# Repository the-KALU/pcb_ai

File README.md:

# PCB-AI

An AI pipeline for generating and optimizing PCB layouts from natural language prompts.

## Project Structure

- `scripts/`: Parsing, training, and testing scripts
- `pcb_projects/`: KiCad files
- `models/`: Saved models

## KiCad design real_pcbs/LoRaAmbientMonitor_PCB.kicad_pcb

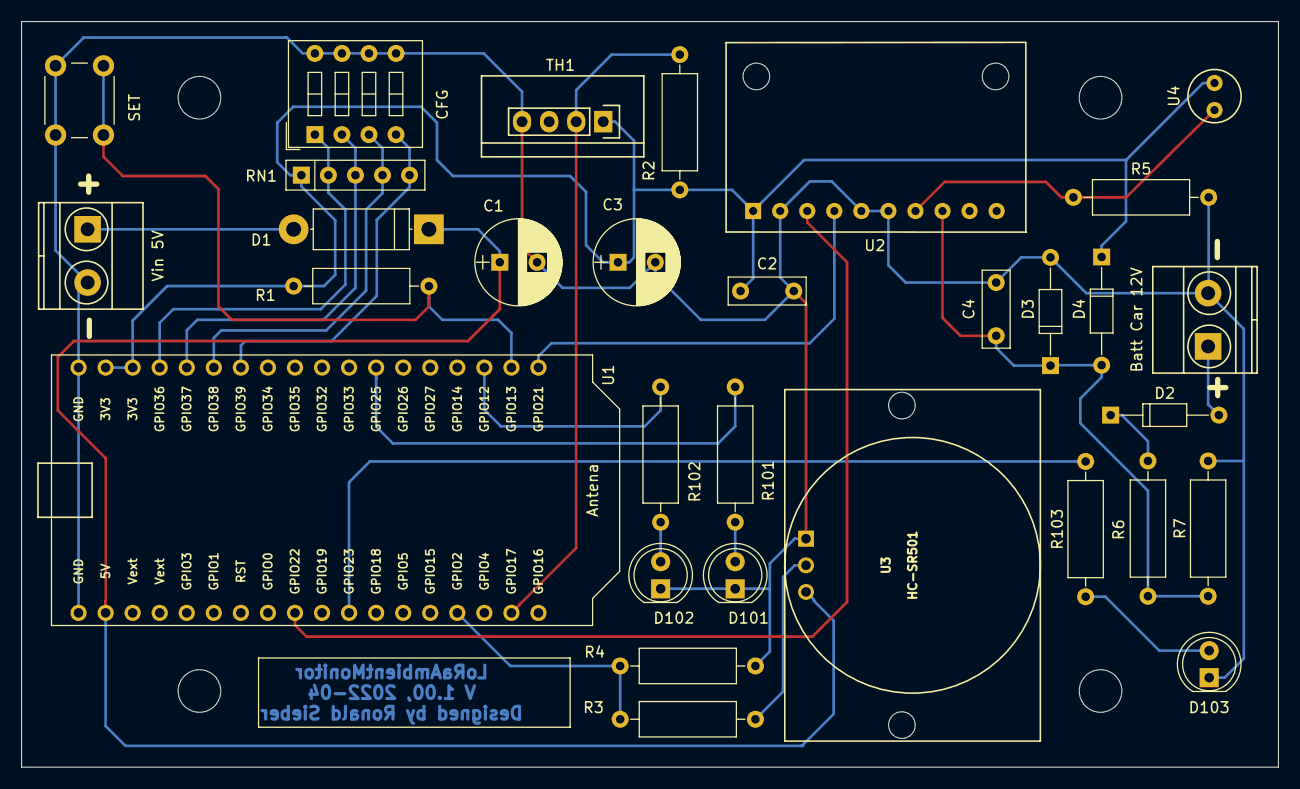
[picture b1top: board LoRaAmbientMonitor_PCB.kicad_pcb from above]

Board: 2 copper layers, 118.0 x 70.0 mm, 31 parts (0 on the bottom side), 24 nets.

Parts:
C1: 100µF; CP_Radial_D8.0mm_P3.50mm
C2, C4: 1µF; C_Rect_L7.2mm_W2.5mm_P5.00mm_FKS2_FKP2_MKS2_MKP2
C3: 47µF; CP_Radial_D8.0mm_P3.50mm
D1: 1N4001; D_5W_P12.70mm_Horizontal
D2: 1N4148; D_DO-35_SOD27_P10.16mm_Horizontal
D3: ZF4,7; D_DO-35_SOD27_P10.16mm_Horizontal
D4: BAT42; D_DO-35_SOD27_P10.16mm_Horizontal
D101, D102, D103: LED; LED_D5.0mm
J1: Vin 5V; TerminalBlock_Phoenix_MKDS1.5-2pol
J2: Batt Car 12V; TerminalBlock_Phoenix_MKDS1.5-2pol
R1, R2, R4: 4k7; R_Axial_DIN0309_L9.0mm_D3.2mm_P12.70mm_Horizontal
R3: 2k7; R_Axial_DIN0309_L9.0mm_D3.2mm_P12.70mm_Horizontal
R5: 100k; R_Axial_DIN0309_L9.0mm_D3.2mm_P12.70mm_Horizontal
R6: 68k; R_Axial_DIN0309_L9.0mm_D3.2mm_P12.70mm_Horizontal
R7: 18k; R_Axial_DIN0309_L9.0mm_D3.2mm_P12.70mm_Horizontal
R101, R102, R103: 470R; R_Axial_DIN0309_L9.0mm_D3.2mm_P12.70mm_Horizontal
RN1: SIL 5-4 4,7K; R_Array_SIP5
SW1: SET; SW_PUSH_6mm_h5mm
SW2: CFG; SW_DIP_x4_W7.62mm_Slide
TH1: DHT22; DHT22_Temperature_Humidity
U1: Heltec_WiFi_LoRa_V2_L; Heltec_WiFi_LoRa_V2
U2: Adafruit_ADS1115
U3: HC-SR501
U4: ALS-PDIC243

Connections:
+3V3: C2.1, C3.1, D4.1, R1.1, R2.2, RN1.1, TH1.1, U1.34, U1.35, U2.1, U4.1
+5V: C1.1, D1.1, U1.2, U3.3
GND: C1.2, C2.2, C3.2, C4.2, D3.2, D101.1, D102.1, D103.1, J1.2, J2.2, R4.2, R5.2, R7.2, SW1.2, SW2.5, SW2.6, SW2.7, SW2.8, TH1.4, U1.1, U1.36, U2.2, U2.5, U2.6, U3.1
unnamed: C4.1, D3.1, D4.2, R6.2, R7.1, U2.8
unnamed: D1.2, J1.1
unnamed: D2.1, R6.1
unnamed: D2.2, J2.1
unnamed: D101.2, R101.1
unnamed: D102.2, R102.1
unnamed: D103.2, R103.1
unnamed: R1.2, SW1.1, U1.20
unnamed: R2.1, TH1.2, U1.17
unnamed: R3.1, U3.2
unnamed: R3.2, R4.1, U1.15
unnamed: R5.1, U2.7, U4.2
unnamed: R101.2, U1.25
unnamed: R102.2, U1.21
unnamed: R103.2, U1.11
unnamed: RN1.2, SW2.1, U1.33
unnamed: RN1.3, SW2.2, U1.32
unnamed: RN1.4, SW2.3, U1.31
unnamed: RN1.5, SW2.4, U1.30
unnamed: U1.9, U2.3
unnamed: U1.19, U2.4

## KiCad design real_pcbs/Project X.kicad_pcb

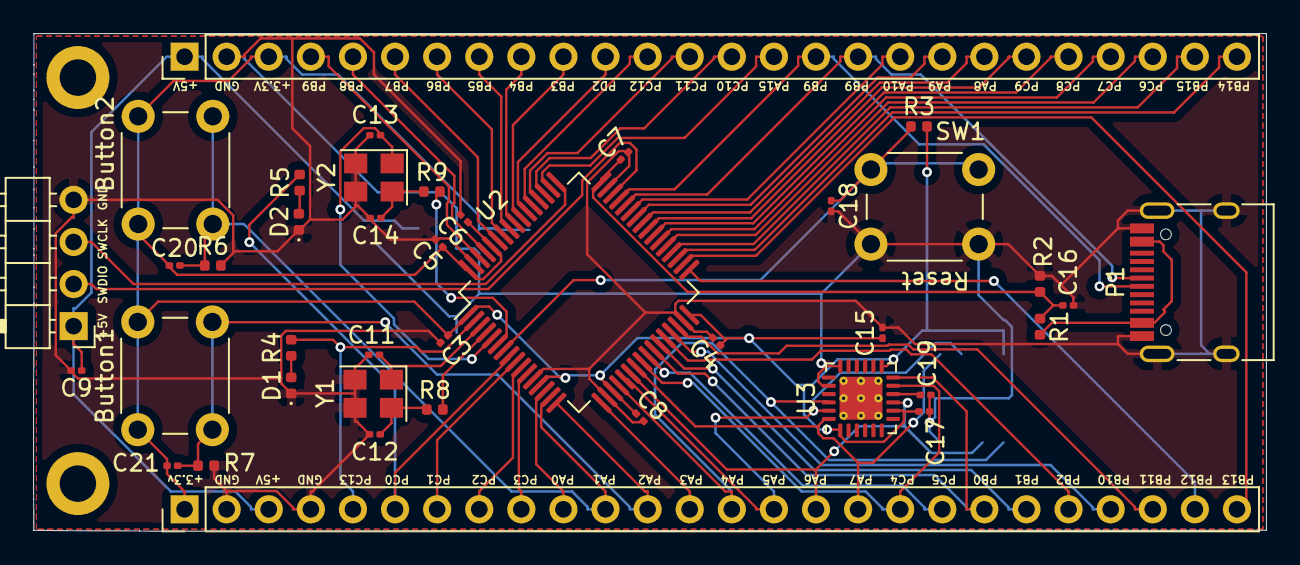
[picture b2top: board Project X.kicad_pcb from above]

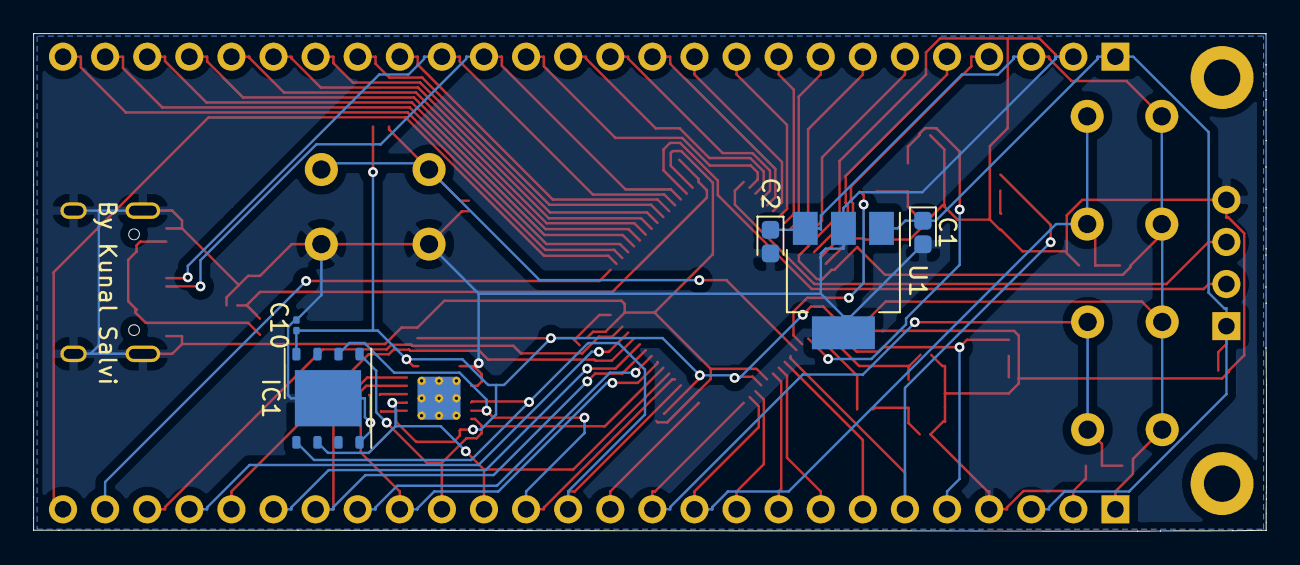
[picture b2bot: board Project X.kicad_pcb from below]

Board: 2 copper layers, 74.4 x 30.0 mm, 46 parts (5 on the bottom side), 62 nets.

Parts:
Button1, Button2: SW_SPST; SW_PUSH_6mm_H5mm
C1, C2: 3.3U; CP_EIA-1608-08_AVX-J
C3, C4, C5, C6, C7, C8, C9: 100N; C_0201_0603Metric
C10, C15, C16, C18, C20, C21: 10N; C_0201_0603Metric
C11, C12, C13, C14: 50P; C_0201_0603Metric
C17, C19: 0.1U; C_0201_0603Metric
D1, D2: LED; LED_0402_1005Metric
IC1: W25Q128JVPIQ; WSON-8-1EP_6x5mm_P1.27mm_EP3.4x4mm
J1: Conn_01x04; PinHeader_1x04_P2.54mm_Horizontal
J2, J3: Conn_01x26; PinHeader_1x26_P2.54mm_Vertical
P1: USB_C_Plug_USB2.0; USB_C_Receptacle_HRO_TYPE-C-31-M-12
R1: 1.1K; R_0402_1005Metric
R2: 2K; R_0402_1005Metric
R3, R4, R5, R6, R7: 4.7K; R_0402_1005Metric
R8, R9: 1M; R_0402_1005Metric
SW1: SW_SPST; SW_PUSH_6mm_H5mm
U1: LT1129-3.3_SOT223; SOT-223-3_TabPin2
U2: STM32L476RCTx; LQFP-64_10x10mm_P0.5mm
U3: MPU-9250; QFN-24-1EP_4x4mm_P0.5mm_EP2.6x2.6mm_ThermalVias
Y1: 8MHz; Crystal_SMD_3225-4Pin_3.2x2.5mm
Y2: 32.768K; Crystal_SMD_3225-4Pin_3.2x2.5mm
mouse-bite-2mm-slot: VAL**; mouse-bite-2mm-slot

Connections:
+3V3: Button1.1, Button2.1, C2.1, C3.1, C4.1, C5.1, C6.1, C8.1, C10.1, C15.1, C17.1, C20.1, C21.1, IC1.8, J2.1, J3.3, R3.1, U1.3, U2.1, U2.13, U2.19, U2.32, U2.60, U2.64, U3.1, U3.8, U3.13
+5V: C1.1, C9.1, J1.1, J2.3, J3.1, U1.1
/D+: J3.16, P1.A6, U2.45
/D-: J3.17, P1.A7, U2.44
/NRST: C18.1, R3.2, SW1.1, U2.7
/OSC8_IN: C13.1, U2.5, Y2.1
/OSC8_OUT: R9.2, U2.6
/OSC32_IN: C11.1, U2.3, Y1.1
/OSC32_OUT: R8.2, U2.4
/PA0: J2.10, U2.14
/PA1: Button2.2, C20.2, J2.11, R6.1, U2.15
/PA2: Button1.2, C21.2, J2.12, R7.1, U2.16
/PA3: J2.13, U2.17
/PA4: IC1.1, J2.14, U2.20, U3.22
/PA5: IC1.6, J2.15, U2.21, U3.23
/PA6: IC1.2, J2.16, U2.22, U3.9
/PA7: IC1.5, J2.17, U2.23, U3.24
/PA8: J3.20, U2.41
/PA9: J3.19, U2.42
/PA10: J3.18, U2.43
/PA15: J3.15, U2.50
/PB0: J2.20, U2.26, U3.12
/PB1: J2.21, U2.27
/PB2: J2.22, U2.28
/PB3: J3.10, U2.55
/PB4: J3.9, U2.56
/PB5: J3.8, U2.57
/PB6: J3.7, U2.58
/PB7: J3.6, U2.59
/PB8: J3.5, U2.61
/PB9: J3.4, U2.62
/PB10: J2.23, U2.29
/PB11: J2.24, U2.30
/PB12: J2.25, U2.33
/PB13: J2.26, U2.34
/PB14: J3.26, U2.35
/PB15: J3.25, U2.36
/PC0: J2.6, R5.2, U2.8
/PC1: J2.7, U2.9
/PC2: J2.8, U2.10
/PC3: J2.9, U2.11
/PC4: J2.18, U2.24, U3.11
/PC5: J2.19, U2.25
/PC6: J3.24, U2.37
/PC7: J3.23, U2.38
/PC8: J3.22, U2.39
/PC9: J3.21, U2.40
/PC10: J3.14, U2.51
/PC11: J3.13, U2.52
/PC12: J3.12, U2.53
/PC13: J2.5, R4.2, U2.2
/PD2: J3.11, U2.54
/SWCLK: J1.3, U2.49
/SWDIO: J1.2, U2.46
/VBUS: C7.1, C16.1, R1.1, R2.2, U2.48
GND: C1.2, C2.2, C3.2, C4.2, C5.2, C6.2, C7.2, C8.2, C9.2, C10.2, C11.2, C12.2, C13.2, C14.2, C15.2, C16.2, C17.2, C18.2, C19.1, D1.1, D2.1, IC1.4, IC1.9, J1.4, J2.2, J2.4, J3.2, P1.A1, P1.A12, P1.B1, P1.B12, P1.S1, R2.1, R6.2, R7.2, SW1.2, U1.2, U2.12, U2.18, U2.31, U2.47, U2.63, U3.18, U3.20, Y1.2, Y1.3, Y2.2, Y2.3
unnamed: C12.1, R8.1, Y1.4
unnamed: C14.1, R9.1, Y2.4
unnamed: C19.2, U3.10
unnamed: D1.2, R4.1
unnamed: D2.2, R5.1
unnamed: P1.A4, P1.A9, P1.B4, P1.B9, R1.2

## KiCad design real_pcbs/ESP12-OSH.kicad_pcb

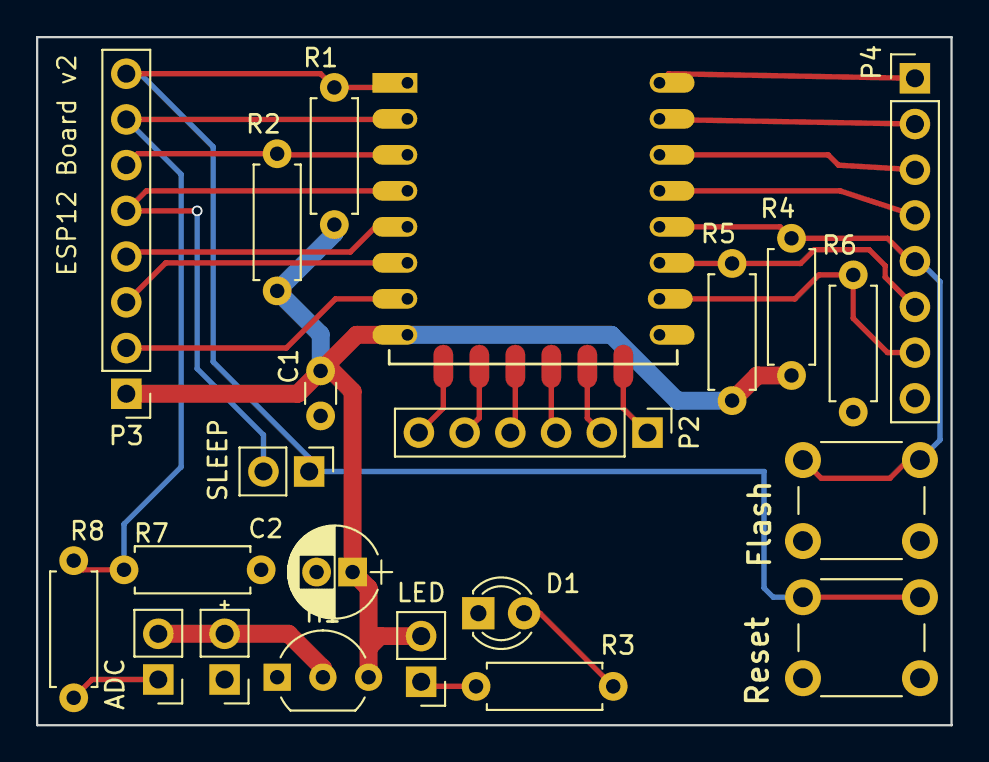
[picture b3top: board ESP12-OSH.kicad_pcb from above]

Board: 2 copper layers, 50.8 x 38.2 mm, 23 parts (1 on the bottom side), 26 nets.

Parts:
ADC: Jumper; Pin_Header_Straight_1x02_Pitch2.54mm
C1: 100nF; C_Disc_D3.0mm_W1.6mm_P2.50mm
C2: 0.1uF; CP_Radial_D5.0mm_P2.00mm
D1: LED; LED_D3.0mm
H1: HT7333; TO-92_Inline_Wide
IN: CONN_01X02; Pin_Header_Straight_1x02_Pitch2.54mm
LED: Jumper; Pin_Header_Straight_1x02_Pitch2.54mm
LOGO: newlogo
P2: CONN_01X06; Pin_Header_Straight_1x06_Pitch2.54mm
P3, P4: CONN_01X08; Pin_Header_Straight_1x08_Pitch2.54mm
R1, R2, R4, R5, R6: 10K; R_Axial_DIN0207_L6.3mm_D2.5mm_P7.62mm_Horizontal
R3: 1K; R_Axial_DIN0207_L6.3mm_D2.5mm_P7.62mm_Horizontal
R7: 100K; R_Axial_DIN0207_L6.3mm_D2.5mm_P7.62mm_Horizontal
R8: 470K; R_Axial_DIN0207_L6.3mm_D2.5mm_P7.62mm_Horizontal
SLEEP: Jumper; Pin_Header_Straight_1x02_Pitch2.54mm
SW1, SW2: SW_Push; SW_PUSH_6mm
U1: ESP-12E

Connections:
/ADC: P3.7, R7.1, R8.2, U1.2
/CH_PD: P3.6, R2.1, U1.3
/CSO: P2.6, U1.17
/GPIO0: P4.5, R4.2, SW2.1, U1.12
/GPIO2: P4.6, R5.2, U1.11
/GPIO4: P4.4, U1.13
/GPIO5: P4.3, U1.14
/GPIO09: P2.4, U1.19
/GPIO10: P2.3, U1.20
/GPIO12: P3.3, U1.6
/GPIO13: P3.2, U1.7
/GPIO14: P3.4, U1.5
/GPIO15: P4.7, R6.2, U1.10
/GPIO16: P3.5, SLEEP.2, U1.4
/MISO: P2.5, U1.18
/MOSI: P2.2, U1.21
/REST: P3.8, R1.1, SLEEP.1, SW1.1, U1.1
/RX: P4.2, U1.15
/SCLK: P2.1, U1.22
/TX: P4.1, U1.16
/VCC: C1.1, C2.1, H1.3, LED.2, P3.1, R1.2, R2.2, R4.1, R5.1, U1.8
/VIN: ADC.2, H1.2, IN.2
GND: C1.2, C2.2, D1.1, H1.1, IN.1, P4.8, R6.1, R7.2, SW1.2, SW2.2, U1.9
unnamed: D1.2, R3.2
unnamed: LED.1, R3.1
unnamed: ADC.1, R8.1

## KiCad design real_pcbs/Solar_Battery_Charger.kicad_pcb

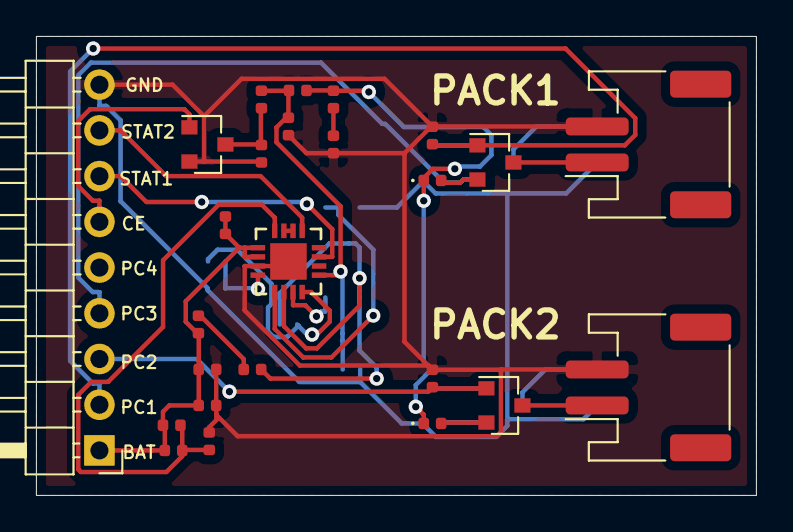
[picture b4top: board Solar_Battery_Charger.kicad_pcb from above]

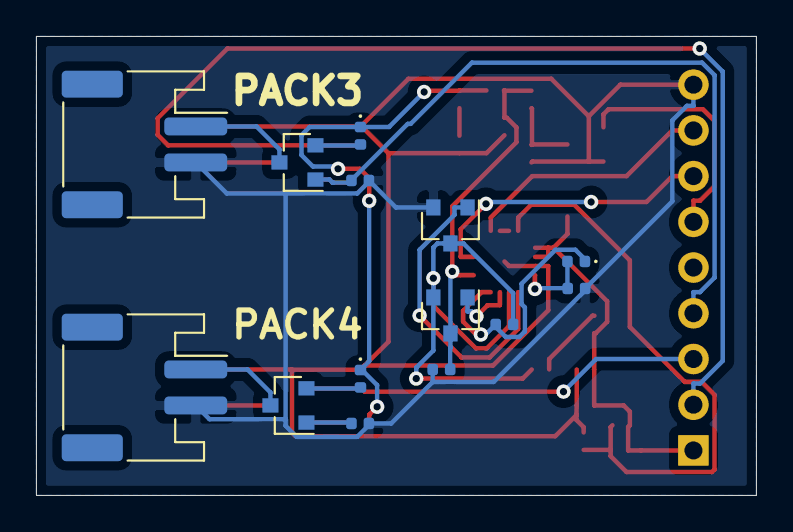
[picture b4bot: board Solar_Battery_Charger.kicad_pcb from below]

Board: 2 copper layers, 40.0 x 25.5 mm, 39 parts (14 on the bottom side), 29 nets.

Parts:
C1: 2.2U; C_0402_1005Metric
C2, C4: 1U; C_0402_1005Metric
C5, C7: 0.1U; C_0402_1005Metric
C6, C8: 10U; C_0402_1005Metric
C9: 4.7U; C_0402_1005Metric
C10: 22P; C_0402_1005Metric
D1, D2, D3, D4: D; D_0402_1005Metric
D5: D_Schottky; D_0402_1005Metric
J1, J2, J3, J4: Conn_01x02; JST_PH_S2B-PH-SM4-TB_1x02-1MP_P2.00mm_Horizontal
J5: Conn_01x09; PinHeader_1x09_P2.54mm_Horizontal
L1: 10U; L_0402_1005Metric
Q1, Q2, Q3, Q4, Q5, Q6, Q7: 2N7002; SOT-23
R1: 100K; R_0402_1005Metric
R2, R3: 499K; R_0402_1005Metric
R4: 36K; R_0402_1005Metric
R5: 2; R_0402_1005Metric
R6: 10; R_0402_1005Metric
RMOS1, RMOS2, RMOS3, RMOS4: 10K; R_0402_1005Metric
RSR1: 20m; R_0402_1005Metric
U1: BQ24650RVAR; QFN50P350X350X100-17N

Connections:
BATTERY_PACK: C7.1, C7.2, C8.1, C9.1, C10.1, J5.1, R2.1, RSR1.2, U1.9, U1.10
BTST: C5.2, D5.1, U1.16
CE: J5.6, Q3.1
GND: C1.2, C2.2, C4.1, C6.2, C8.2, C9.2, J1.2, J2.2, J3.2, J4.2, J5.9, Q2.2, Q3.2, R1.2, R4.1, RMOS1.2, RMOS2.2, RMOS3.2, RMOS4.2, U1.11, U1.17
unnamed: C1.1, R5.1
unnamed: D1.1, D2.1, D3.1, D4.1, R5.2, R6.2
unnamed: D1.2, Q4.2
unnamed: D2.2, Q5.2
unnamed: D3.2, Q6.2
unnamed: D4.2, Q7.2
unnamed: J1.1, Q4.3
unnamed: J2.1, Q5.3
unnamed: J3.1, Q6.3
unnamed: J4.1, Q7.3
unnamed: L1.2, RSR1.1
unnamed: Q1.1, U1.15
unnamed: Q2.1, U1.13
unnamed: Q3.3, R3.1, R4.2, U1.2
unnamed: U1.6, U1.7
PACK1_CONTROL: J5.2, Q4.1, RMOS1.1
PACK2_CONTROL: J5.3, Q5.1, RMOS2.1
PACK3_CONTROL: J5.4, Q6.1, RMOS3.1
PACK4_CONTORL: Q7.1, RMOS4.1
PH: C5.1, L1.1, Q1.2, Q2.3, U1.14
REGN: C4.2, D5.2, U1.12
STAT1: J5.7, U1.3
STAT2: J5.8, U1.5
VCC_PACK: C2.1, C6.1, Q1.3, R3.2, R6.1, U1.1
VFB: C10.2, R1.1, R2.2, U1.8

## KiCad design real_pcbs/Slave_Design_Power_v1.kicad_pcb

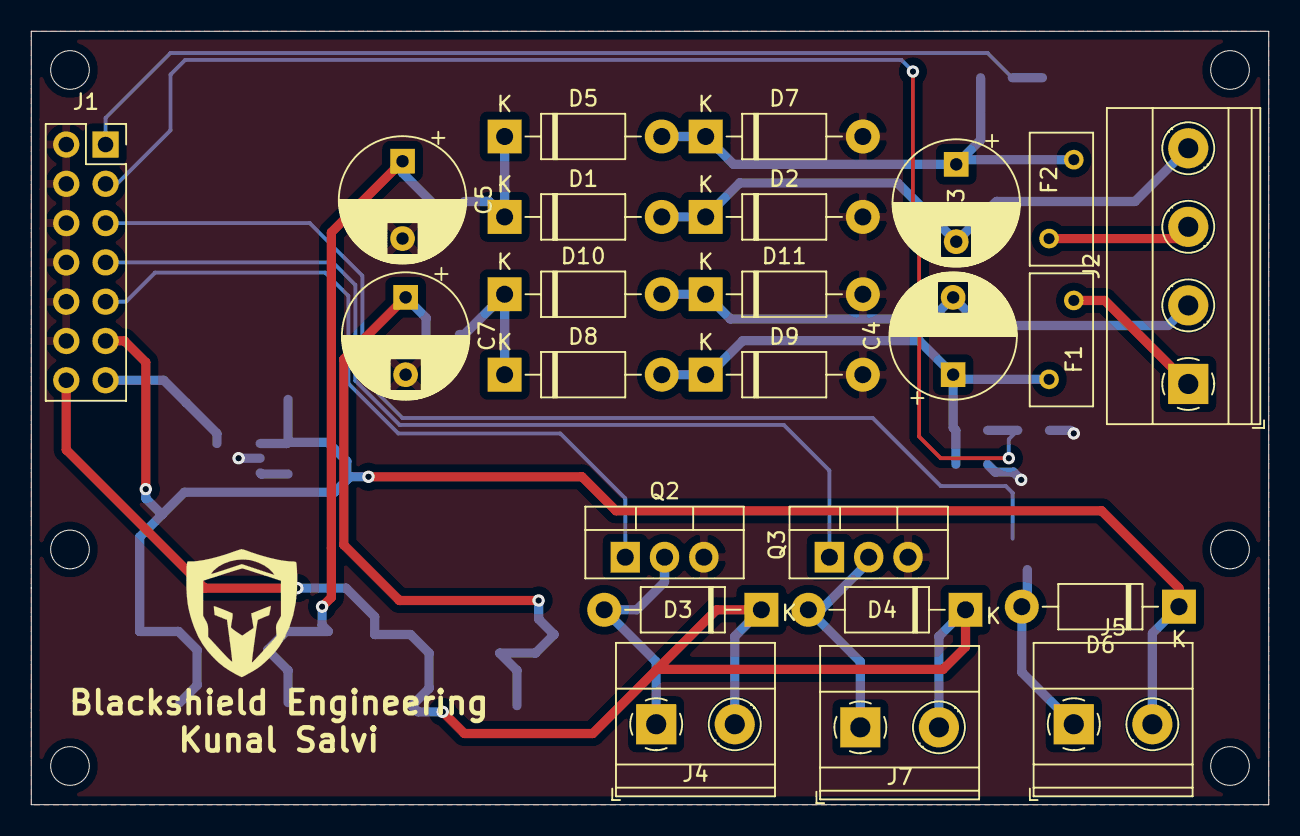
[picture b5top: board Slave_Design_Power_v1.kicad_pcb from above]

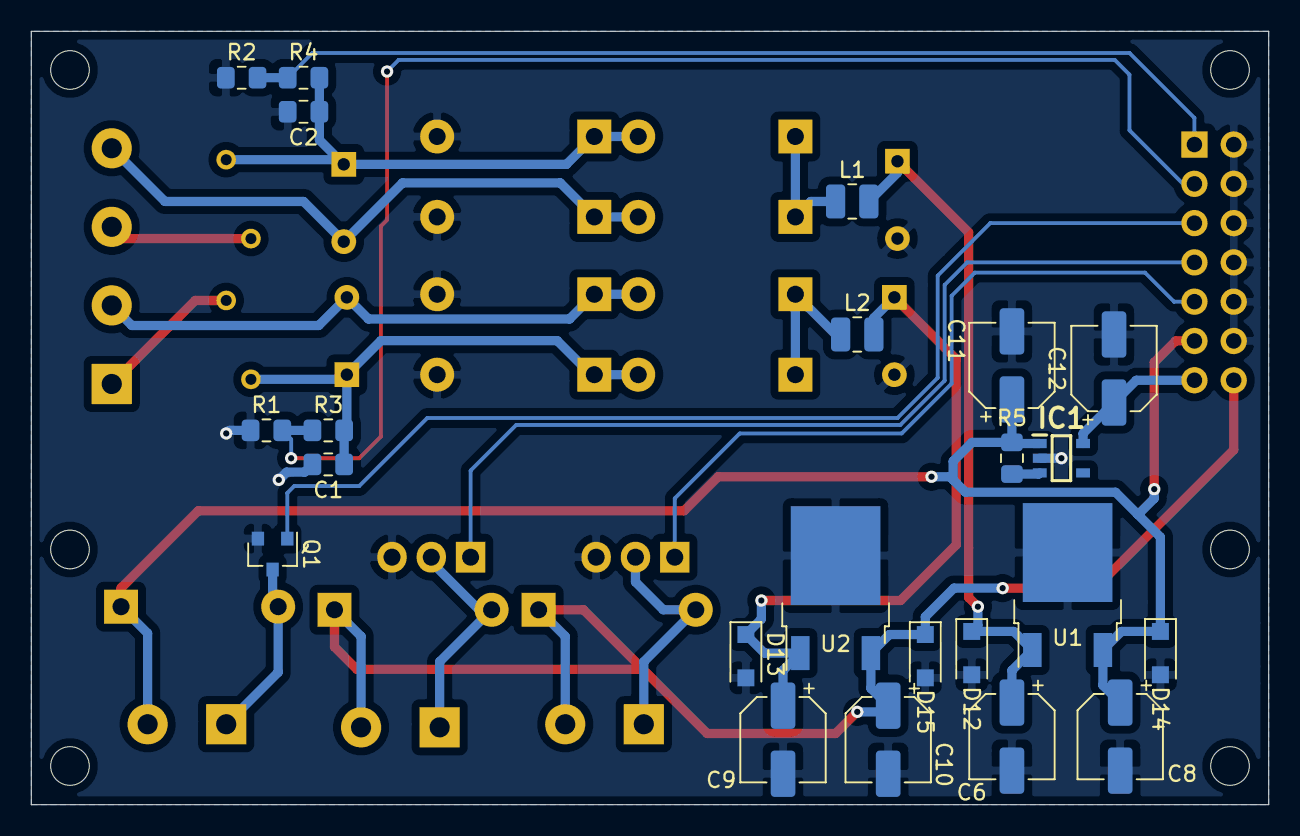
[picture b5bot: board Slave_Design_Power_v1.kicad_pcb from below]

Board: 2 copper layers, 80.0 x 50.0 mm, 47 parts (23 on the bottom side), 23 nets.

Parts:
C1, C2: C; C_0805_2012Metric_Pad1.15x1.40mm_HandSolder
C3, C4, C5, C7: 47uF; CP_Radial_D8.0mm_P5.00mm
C6, C8, C9, C10: 1uF; CP_Elec_5x4.5
C11: 0.1uF; CP_Elec_5x4.5
C12: 1.0uF; CP_Elec_5x4.5
D1, D2, D3, D4, D5, D6, D7, D8, D9, D10, D11: 1N4002; D_DO-41_SOD81_P10.16mm_Horizontal
D12, D13, D14, D15: MM3Z18VST1G; D_SOD-123F
F1, F2: Fuse; Fuse_BelFuse_0ZRE0005FF_L8.3mm_W3.8mm
IC1: NJM2866F05-TE1; SOT95P280X130-5N
J1: Conn_02x07_Odd_Even; PinSocket_2x07_P2.54mm_Vertical
J2: Screw_Terminal_01x04; TerminalBlock_Phoenix_MKDS-1,5-4-5.08_1x04_P5.08mm_Horizont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
J4, J5, J7: Screw_Terminal_01x02; TerminalBlock_Phoenix_MKDS-1,5-2-5.08_1x02_P5.08mm_Horizont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
L1, L2: 1239AS-H-1R0M=P2; L_1008_2520Metric
Q1: BC817; SOT-23
Q2, Q3: TIP122; TO-220-3_Vertical
R1, R2, R3, R4, R5: 100; R_0805_2012Metric_Pad1.15x1.40mm_HandSolder
U1: MC78M12CDTG; TO-252-2
U2: MC78M18CDTG; TO-252-2

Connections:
5V: C12.1, IC1.5, J1.13
12V: C8.1, C11.1, D6.1, D14.1, IC1.1, J1.11, J5.2, R5.2, U1.3
12V_RELAY: J1.5, Q1.1
12_IND: J1.3, R1.2, R3.1
18V: C10.1, D3.1, D4.1, D15.1, J1.14, J4.2, J7.2, U2.3
18V_RELAY_1: J1.9, Q2.1
18V_RELAY_2: J1.7, Q3.1
18_IND: J1.1, R2.2, R4.1
GND: C1.2, C2.2, C5.2, C6.2, C7.2, C8.2, C9.2, C10.2, C11.2, C12.2, D2.2, D7.2, D9.2, D11.2, D12.2, D13.2, D14.2, D15.2, IC1.2, J1.2, J1.4, J1.6, J1.8, J1.10, J1.12, Q1.2, Q2.3, Q3.3, R1.1, R2.1, U1.2, U2.2
unnamed: C1.1, C4.1, D8.2, D9.1, F1.2, R3.2
unnamed: C2.1, C3.1, D5.2, D7.1, F2.2, R4.2
unnamed: C3.2, D1.2, D2.1, J2.4
unnamed: C4.2, D10.2, D11.1, J2.2
unnamed: C5.1, C6.1, D12.1, L1.2, U1.1
unnamed: C7.1, C9.1, D13.1, L2.2, U2.1
unnamed: D1.1, D5.1, L1.1
unnamed: D3.2, J4.1, Q2.2
unnamed: D4.2, J7.1, Q3.2
unnamed: D6.2, J5.1, Q1.3
unnamed: D8.1, D10.1, L2.1
unnamed: F1.1, J2.1
unnamed: F2.1, J2.3
unnamed: IC1.3, R5.1

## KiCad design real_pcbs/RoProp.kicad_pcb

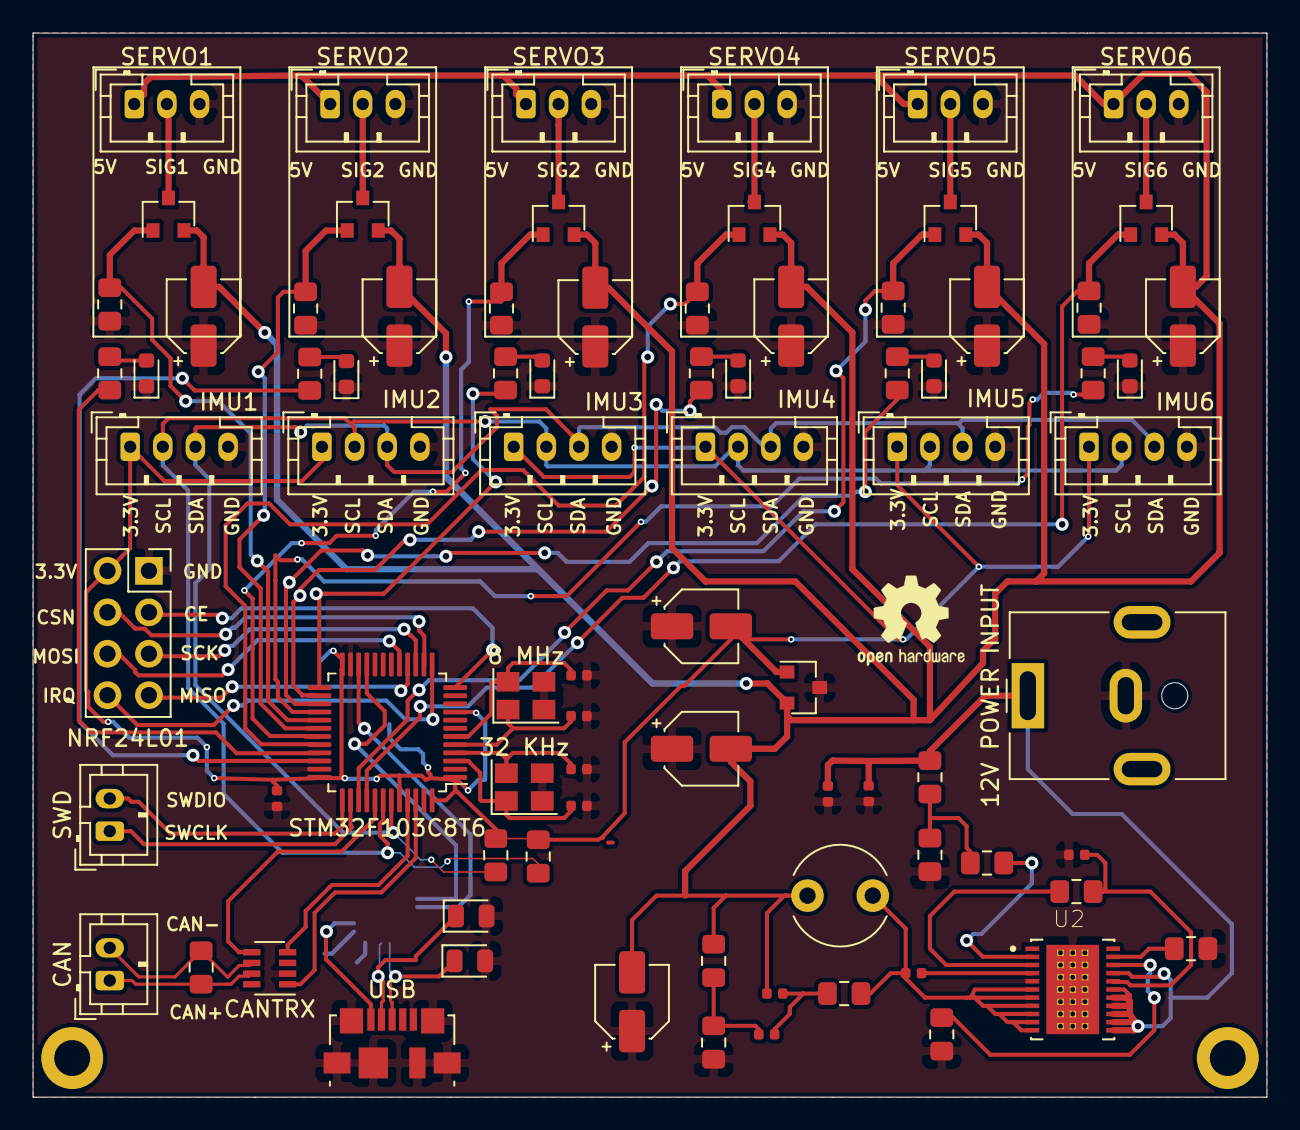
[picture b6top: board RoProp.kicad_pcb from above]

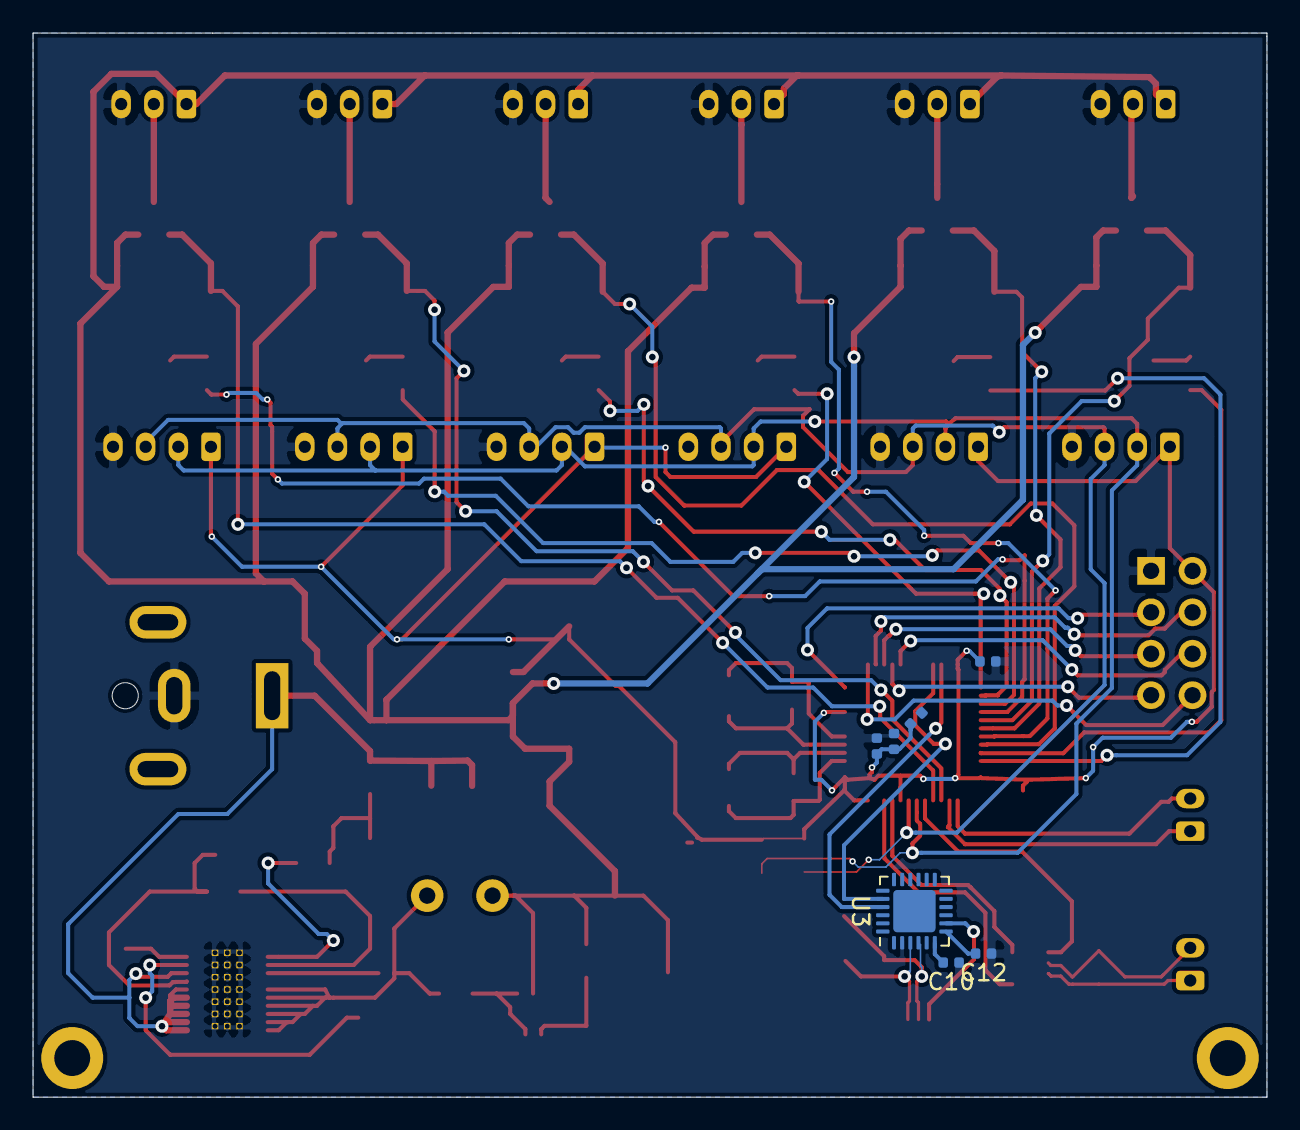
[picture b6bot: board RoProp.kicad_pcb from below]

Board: 2 copper layers, 75.6 x 65.2 mm, 89 parts (7 on the bottom side), 62 nets.

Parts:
8 MHz, 32 KHz: Crystal_GND23; Crystal_SMD_Abracon_ABM8G-4Pin_3.2x2.5mm
12V POWER INPUT: Barrel_Jack; BarrelJack_CUI_PJ-063AH_Horizontal
C1, C2: 4.7U; C_0402_1005Metric
C3, C4, C5, C6, C7: 10N; C_0402_1005Metric
C8: 1U; C_0402_1005Metric
C9, C17: 100N; C_0402_1005Metric
C10, C11, C12, C13, C14, C15, C16: 1N; C_0402_1005Metric
C18: 100U; CP_Elec_4x3
C19, C23: 1N; CP_Elec_4x3
C20, C21, C22, C24, C25, C26: 2U; CP_Elec_4x3
CAN: Conn_01x02; JST_PH_B2B-PH-K_1x02_P2.00mm_Vertical
CANTRX: TCAN330; SOT-23-8
D1, D2, D3, D4, D5, D6: LED; LED_0603_1608Metric
D7, D8: D_TVS; D_0805_2012Metric
IMU1, IMU2, IMU3, IMU4, IMU5, IMU6: Conn_01x04; JST_PH_B4B-PH-K_1x04_P2.00mm_Vertical
L1: 4.7U; L_Radial_D6.0mm_P4.00mm
NRF24L01: Conn_02x04_Odd_Even; PinSocket_2x04_P2.54mm_Vertical
Q1, Q2, Q3, Q4, Q5, Q6: DMN2056U; SOT-23
R1, R2: 4.7K; R_0805_2012Metric_Pad1.15x1.40mm_HandSolder
R3: 854K; R_0805_2012Metric_Pad1.15x1.40mm_HandSolder
R4: 86.6K; R_0805_2012Metric_Pad1.15x1.40mm_HandSolder
R5: 1K; R_0805_2012Metric_Pad1.15x1.40mm_HandSolder
R6, R7, R11: 105K; R_0805_2012Metric_Pad1.15x1.40mm_HandSolder
R8, R9, R10, R12, R13, R14, R15: 1.91K; R_0805_2012Metric_Pad1.15x1.40mm_HandSolder
R16: 69.8K; R_0805_2012Metric_Pad1.15x1.40mm_HandSolder
R17: 10K; R_0805_2012Metric_Pad1.15x1.40mm_HandSolder
R18, R19, R20, R21, R22, R23: 2k; R_0805_2012Metric_Pad1.15x1.40mm_HandSolder
R24: 120; R_0805_2012Metric_Pad1.15x1.40mm_HandSolder
SERVO1, SERVO2, SERVO3, SERVO4, SERVO5, SERVO6: Conn_01x03; JST_PH_B3B-PH-K_1x03_P2.00mm_Vertical
STM32F103C8T6: STM32F103C8Tx; LQFP-48_7x7mm_P0.5mm
SWD: Conn_01x02; JST_PH_B2B-PH-K_1x02_P2.00mm_Vertical
U2: TPS53318DQPR; CONV_TPS53318DQPR
U3: CP2102N-A01-GQFN24; QFN-24-1EP_4x4mm_P0.5mm_EP2.6x2.6mm
U4: LM3480-3.3; SOT-23
USB: USB_B_Micro; USB_Micro-B_Molex_47346-0001

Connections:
+3V3: C3.1, C4.1, C5.2, C6.2, C7.2, C10.2, C12.2, C23.2, CANTRX.3, IMU1.1, IMU2.1, IMU3.1, IMU4.1, IMU5.1, IMU6.1, NRF24L01.2, R1.1, R2.1, STM32F103C8T6.1, STM32F103C8T6.9, STM32F103C8T6.24, STM32F103C8T6.36, STM32F103C8T6.44, STM32F103C8T6.48, U3.5, U3.6, U3.7, U4.1
+5V: C17.1, C18.2, C19.2, C20.2, C21.2, C22.2, C24.2, C25.2, C26.2, L1.2, Q1.2, Q2.2, Q3.2, Q4.2, Q5.2, Q6.2, R16.2, SERVO1.1, SERVO2.1, SERVO3.1, SERVO4.1, SERVO5.1, SERVO6.1, U4.2
/CAN+: CAN.1, CANTRX.7, R24.1
/CAN-: CAN.2, CANTRX.6, R24.2
/CANRX: CANTRX.4, STM32F103C8T6.45
/CANTX: CANTRX.1, STM32F103C8T6.46
/CE: NRF24L01.3, STM32F103C8T6.12
/CSN: NRF24L01.4, STM32F103C8T6.14
/D+: D8.1, U3.3, USB.3
/D-: D7.1, U3.4, USB.2
/IRQ: NRF24L01.8, STM32F103C8T6.13
/LED1: R8.2, STM32F103C8T6.33
/LED2: R9.2, STM32F103C8T6.34
/LED3: R10.2, STM32F103C8T6.25
/LED4: R12.2, STM32F103C8T6.26
/LED5: R13.2, STM32F103C8T6.27
/LED6: R14.2, STM32F103C8T6.28
/MISO: NRF24L01.7, STM32F103C8T6.16
/MOSI: NRF24L01.6, STM32F103C8T6.17
/OSC_8_IN: 8 MHz.1, C16.1, STM32F103C8T6.5
/OSC_8_OUT: 8 MHz.4, C14.1, STM32F103C8T6.6
/OSC_32_IN: 32 KHz.1, C15.1, STM32F103C8T6.3
/OSC_32_OUT: 32 KHz.4, C13.1, STM32F103C8T6.4
/PWM1: Q1.1, R18.1, STM32F103C8T6.29
/PWM2: Q4.1, R21.1, STM32F103C8T6.30
/PWM3: Q2.1, R19.1, STM32F103C8T6.31
/PWM4: Q5.1, R22.1, STM32F103C8T6.32
/PWM5: Q3.1, R20.1, STM32F103C8T6.39
/PWM6: Q6.1, R23.1, STM32F103C8T6.40
/RX: STM32F103C8T6.22, U3.21
/SCK: NRF24L01.5, STM32F103C8T6.15
/SCL: IMU1.2, IMU2.2, IMU3.2, IMU4.2, IMU5.2, IMU6.2, R1.2, STM32F103C8T6.42
/SDA: IMU1.3, IMU2.3, IMU3.3, IMU4.3, IMU5.3, IMU6.3, R2.2, STM32F103C8T6.43
/SERVO1: Q1.3, SERVO1.2
/SERVO2: Q4.3, SERVO2.2
/SERVO3: Q2.3, SERVO3.2
/SERVO4: Q5.3, SERVO4.2
/SERVO5: Q3.3, SERVO5.2
/SERVO6: Q6.3, SERVO6.2
/SHDN: CANTRX.5, STM32F103C8T6.41
/SWCLK: STM32F103C8T6.38, SWD.1
/SWDIO: STM32F103C8T6.37, SWD.2
/TX: STM32F103C8T6.21, U3.20
/VBUS: U3.8, USB.1
/VFB: C11.2, R16.1, R17.2, U2.1
/VIN: 12V POWER INPUT.1, C1.2, C2.2, R3.1, U2.12, U2.13, U2.14, U2.15, U2.16, U2.17, U2.19
GND: 8 MHz.2, 8 MHz.3, 12V POWER INPUT.2, 32 KHz.2, 32 KHz.3, C1.1, C2.1, C3.2, C4.2, C5.1, C6.1, C7.1, C8.1, C10.1, C12.1, C13.2, C14.2, C15.2, C16.2, C18.1, C19.1, C20.1, C21.1, C22.1, C23.1, C24.1, C25.1, C26.1, CANTRX.2, D1.1, D2.1, D3.1, D4.1, D5.1, D6.1, D7.2, D8.2, IMU1.4, IMU2.4, IMU3.4, IMU4.4, IMU5.4, IMU6.4, NRF24L01.1, R4.2, R6.2, R7.2, R17.1, R18.2, R19.2, R20.2, R21.2, R22.2, R23.2, SERVO1.3, SERVO2.3, SERVO3.3, SERVO4.3, SERVO5.3, SERVO6.3, STM32F103C8T6.7, STM32F103C8T6.8, STM32F103C8T6.23, STM32F103C8T6.35, STM32F103C8T6.47, U2.5, U2.23, U2.TV1, U2.TV2, U2.TV3, U2.TV4, U2.TV5, U2.TV6, U2.TV7, U2.TV8, U2.TV9, U2.TV10, U2.TV11, U2.TV12, U2.TV13, U2.TV14, U2.TV15, U2.TV16, U2.TV17, U2.TV18, U2.TV19, U2.TV20, U2.TV21, U3.2, U3.25, U4.3, USB.5, USB.6
unnamed: C8.2, R11.2, U2.18
unnamed: C9.1, L1.1, R15.2, U2.6, U2.7, U2.8, U2.9, U2.10, U2.11
unnamed: C9.2, U2.4
unnamed: C11.1, C17.2, R15.1
unnamed: D1.2, R8.1
unnamed: D2.2, R9.1
unnamed: D3.2, R10.1
unnamed: D4.2, R12.1
unnamed: D5.2, R13.1
unnamed: D6.2, R14.1
unnamed: R3.2, R4.1, R5.1
unnamed: R5.2, U2.2
unnamed: R6.1, U2.20
unnamed: R7.1, U2.21
unnamed: R11.1, U2.3

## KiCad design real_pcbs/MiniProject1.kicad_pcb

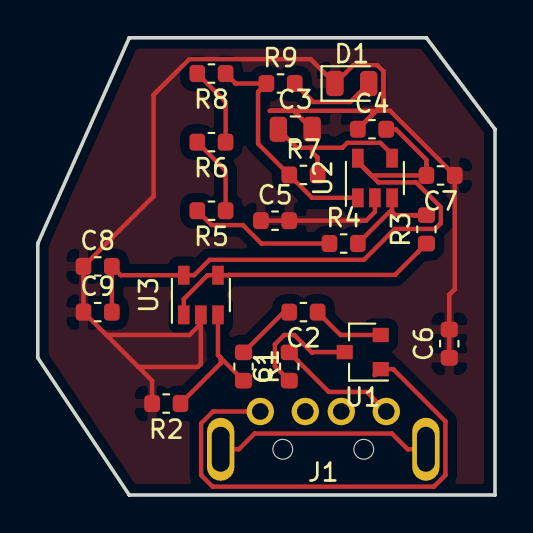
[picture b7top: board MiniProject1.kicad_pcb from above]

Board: 2 copper layers, 25.4 x 25.4 mm, 23 parts (0 on the bottom side), 16 nets.

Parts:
C1, C2: 1 u; C_0603_1608Metric
C3: 10 u; C_0805_2012Metric
C4, C5, C8: .1 u; C_0603_1608Metric
C6, C7, C9: 1 n; C_0603_1608Metric
D1: LED; LED_0805_2012Metric
J1: USB_A; USBA
R1, R2: 4.02 k; R_0603_1608Metric
R3, R8: 100; R_0603_1608Metric
R4: 30.1; R_0603_1608Metric
R5: 20; R_0603_1608Metric
R6: 158; R_0603_1608Metric
R7: 100 k; R_0603_1608Metric
R9: 806; R_0603_1608Metric
U1: LinearReg; SOT-23
U2, U3: OpAmp; SOT-23-5

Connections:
+3V3: C4.2, C7.2, C8.2, C9.2, U2.5, U3.5
GND: C3.2, C4.1, C5.1, C5.2, C6.1, C6.2, C7.1, C8.1, C9.1, D1.1, R2.2, U2.2, U3.2
unnamed: C1.1, U1.3
unnamed: C1.2, J1.1
unnamed: C2.1, U1.2
unnamed: C2.2, R1.1
unnamed: C3.1, R7.2, U2.4
unnamed: D1.2, R9.2
unnamed: J1.4, U1.1
unnamed: R1.2, R2.1, U3.3
unnamed: R3.1, U3.1, U3.4
unnamed: R3.2, R4.2, U2.3
unnamed: R4.1, R5.2
unnamed: R5.1, R6.2
unnamed: R6.1, R8.2
unnamed: R7.1, R8.1, R9.1, U2.1
